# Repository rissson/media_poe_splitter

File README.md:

# Media PoE splitter

This board splits a PoE+ input into a 24V 85W output and a USB interface for data. It is meant to be used as part of my
home media system for driving in-wall speakers.

## Specs

- Uses a [Silvertel Ag5800](https://silvertel.com/ag5800/) for PoE control and DC-DC conversion
  - From PoE+ to PoE++ (Type 2 to Type 4, 802.3at and 802.3bt)
  - Outputs up to 85W of power over 24V
- Converts the data from 4 pairs Ethernet to USB 2.0 with a [Microchip 7850](https://www.microchip.com/en-us/product/lan7850)
  - 10/100/1000 Ethernet (but limited by USB 2.0 speed at around 400 Mbps)

## Usage

My usage of this board is with a
[HiFiBerry Amp2](https://www.hifiberry.com/shop/boards/dealing-with-blocked-p5-holes-7/) and a
[Raspberry Pi Zero 2 W](https://www.raspberrypi.com/products/raspberry-pi-zero-2-w/).

Power is provided to the Amp2, which in turns powers the RPi and drives 2 speakers.

Data is provided to the RPi via Micro USB 2.0. The data output of the `media_poe_splitter` is done over a flex ribbon
cable (pitch 0.5mm, 6pos) to fit dimension constraints. The associated `usb_breakout` board transforms that into a Micro
USB connector that can be plugged in the RPi data port.

## Considerations

Thermal management should be done accordingly to the recommendations provided by the Ag5800 documentation.

The board has 4 heat pads which should be coated using thermally conductive oxime board mounting the Ag5800.

## Datasheets and reference boards

- Ag5800
  - https://silvertel.com/images/datasheets/Ag5800-datasheet-%20IEEE802_3bt-Power-over-Ethernet-4-pair-PD.pdf
  - The EVALAg5800 schematic and BOMs are not publicly published by Silvertel, but they sent it over by email when asked
    for it. As such, I won't reproduce them here, but here are some public references for similar boards:
    - https://silvertel.com/images/Eval-Board-User-Guides/EVALAg5810-User-Manual.pdf
    - https://silvertel.com/images/Eval-Board-User-Guides/EvalAg59600-Board-User-Manual.pdf
- LAN7850
  - https://ww1.microchip.com/downloads/aemDocuments/documents/UNG/ProductDocuments/DataSheets/LAN7850-Data-Sheet-DS00001993F.pdf
  - https://www.farnell.com/datasheets/3109926.pdf
  - https://ww1.microchip.com/downloads/aemDocuments/documents/UNG/ProductDocuments/BoardDesignFiles/UNG8002_EVB_LAN7850_A1.pdf
- Wurth Elektronik PoE Ethernet to USB board
  - https://www.we-online.com/components/media/o758720v410%20RD022_EN.pdf

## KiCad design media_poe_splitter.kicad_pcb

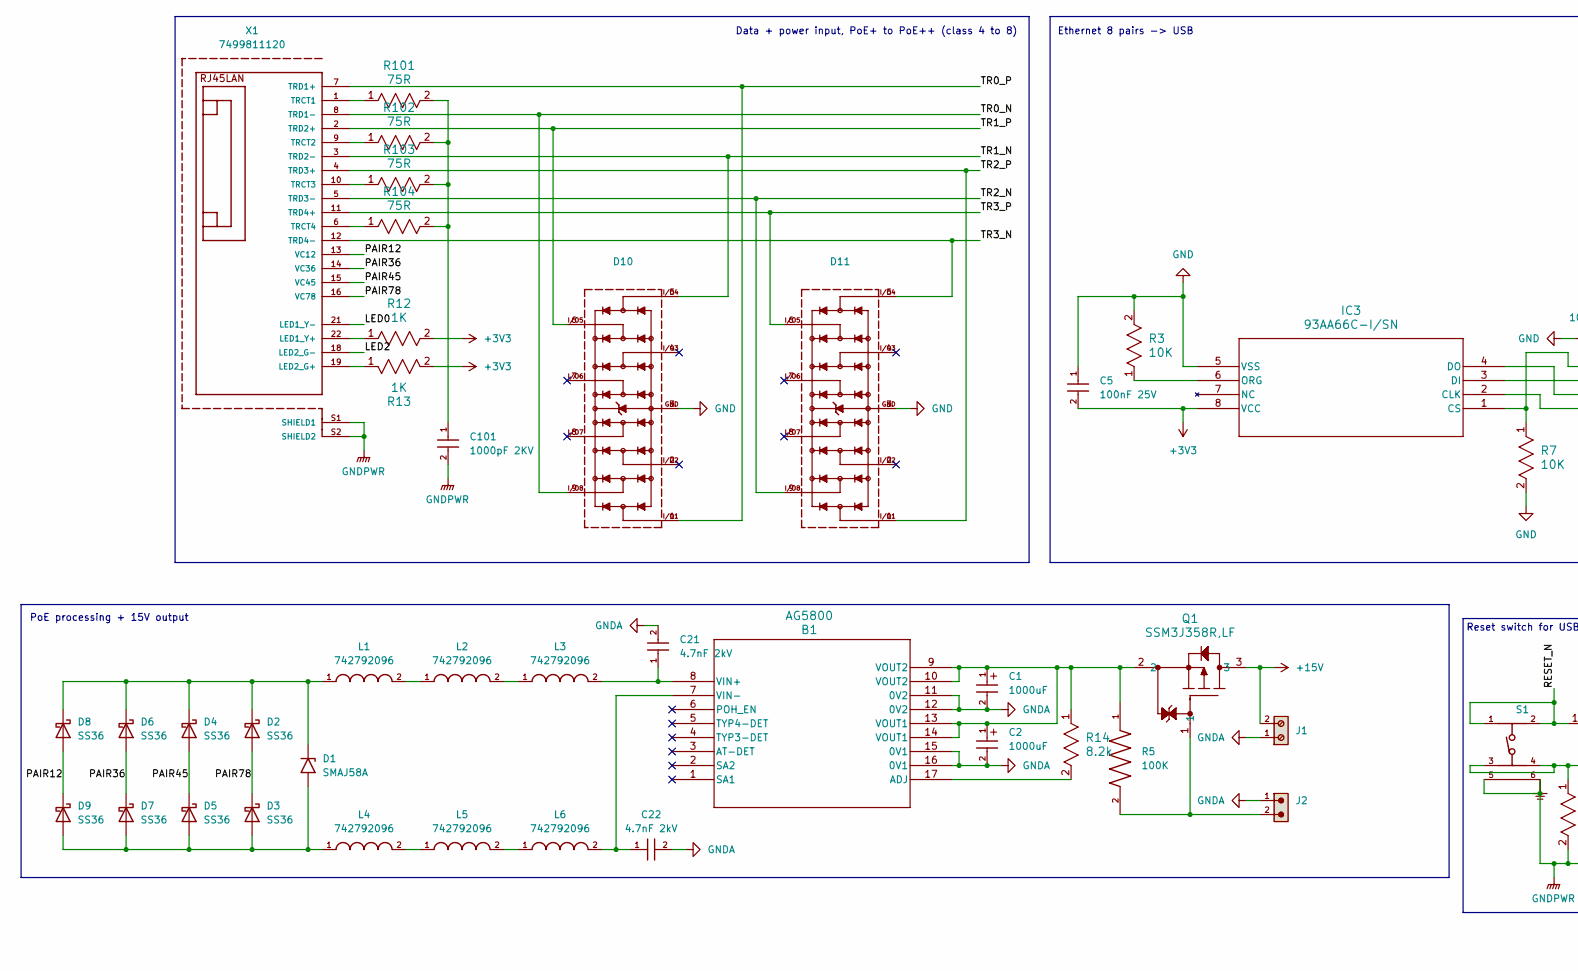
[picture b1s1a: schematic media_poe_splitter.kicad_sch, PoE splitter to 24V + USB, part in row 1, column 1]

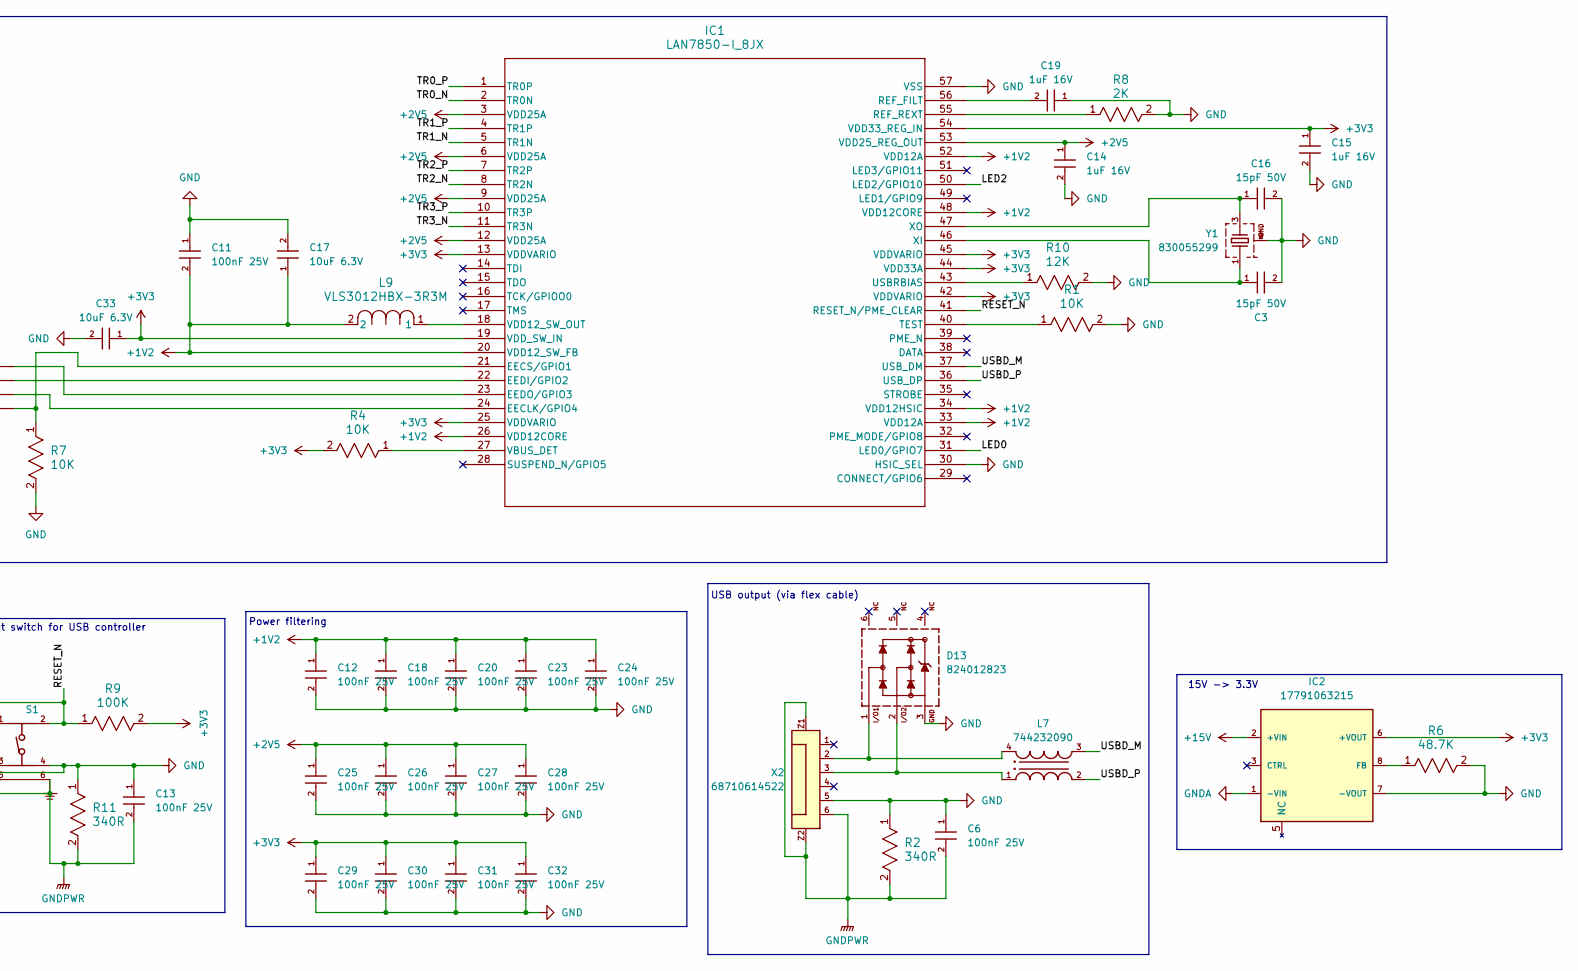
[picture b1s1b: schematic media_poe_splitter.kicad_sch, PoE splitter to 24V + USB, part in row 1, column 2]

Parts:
B1: AG5800; MPN Ag5800
C1, C2: 1000uF; 860020578018; MPN 860020578018
C3, C16: 15pF 50V; 885012005056; MPN 885012005056
C5, C6, C11, C12, C13, C18, C20, C23, C24, C25, C26, C27, C28, C29, C30, C31, C32: 100nF 25V; 885012206071; MPN 885012206071
C14, C15, C19: 1uF 16V; 885012206052; MPN 885012206052
C17, C33: 10uF 6.3V; 885012207003; MPN 885012207003
C21, C22: 4.7nF 2kV; 885342208020; MPN 885342208020
C101: 1000pF 2KV; 885342208024; MPN 885342208024
D1: SMAJ58A; D_SMA; MPN SMAJ58A
D2, D3, D4, D5, D6, D7, D8, D9: SS36; D_SMA; MPN SS36
D10, D11: 5Vdc; 824014885; MPN 824014885
D13: 824012823; MPN 824012823
IC1: LAN7850-I_8JX; MPN LAN7850-I/8JX
IC2: 17791063215; MPN 17791063215
IC3: 93AA66C-I/SN; 93AA66C-I_SN; MPN 93AA66C-I/SN
J1: Screw_Terminal_01x02; 691210910002; MPN 691210910002
J2: 61300211121; PART-NUMBER 61300211121
L1, L2, L3, L4, L5, L6: 742792096; MPN 742792096
L7: 744232090; MPN 744232090
L9: VLS3012HBX-3R3M; MPN VLS3012HBX-3R3M
Q1: SSM3J358R,LF; MPN SSM3J358R,LF
R1, R3, R4, R7: 10K; RC0603FR-0710KL; MPN RC0603FR-0710KL
R2, R11: 340R; RC0603FR-07340RL; MPN RC0603FR-07340RL
R5: 100K; RC1206FR-07100KL; MPN RC1206FR-07100KL
R6: 48.7K; RC0603FR-0748K7L; MPN RC0603FR-0748K7L
R8: 2K; RC0603FR-072KL; MPN RC0603FR-072KL
R9: 100K; RC0603FR-07100KL; MPN RC0603FR-07100KL
R10: 12K; RC0603FR-0712KL; MPN RC0603FR-0712KL
R12, R13: 1K; RC1206FR-071KL; MPN RC1206FR-071KL
R14: 8.2k; RC0603FR-078K2L; MPN RC0603FR-078K2L
R101, R102, R103, R104: 75R; RC0805FR-0775RL; MPN RC0805FR-0775RL
S1: 435151014824; MPN 435151014824
X1: 7499811120; MPN 7499811120
X2: 68710614522; MPN 68710614522
Y1: 830055299; MPN 830055299

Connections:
+1V2: C11.2, C12.1, C17.1, C18.1, C20.1, C23.1, C24.1, IC1.20 (VDD12_SW_FB), IC1.26 (VDD12CORE), IC1.33 (VDD12A), IC1.34 (VDD12HSIC), IC1.48 (VDD12CORE), IC1.52 (VDD12A), L9.2
+2V5: C14.1, C25.1, C26.1, C27.1, C28.1, IC1.3 (VDD25A), IC1.6 (VDD25A), IC1.9 (VDD25A), IC1.12 (VDD25A), IC1.53 (VDD25_REG_OUT)
+3V3: C5.2, C15.1, C29.1, C30.1, C31.1, C32.1, C33.1, IC1.13 (VDDVARIO), IC1.19 (VDD_SW_IN), IC1.25 (VDDVARIO), IC1.42 (VDDVARIO), IC1.44 (VDD33A), IC1.45 (VDDVARIO), IC1.54 (VDD33_REG_IN), IC2.6 (+VOUT), IC3.8 (VCC), R4.2, R9.2, R12.2, R13.2
+15V: IC2.2 (+VIN), J1.2, Q1.3
/LED0: IC1.31 (LED0/GPIO7), X1.21 (LED1_Y-)
/LED2: IC1.50 (LED2/GPIO10), X1.18 (LED2_G-)
/PAIR12: D8.2 (A), D9.1 (K), X1.13 (VC12)
/PAIR36: D6.2 (A), D7.1 (K), X1.14 (VC36)
/PAIR45: D4.2 (A), D5.1 (K), X1.15 (VC45)
/PAIR78: D2.2 (A), D3.1 (K), X1.16 (VC78)
/RESET_N: IC1.41 (RESET_N/PME_CLEAR), R9.1, S1.1, S1.2
/TR0_N: D10.9, IC1.2 (TR0N), X1.8 (TRD1-)
/TR0_P: D10.1, IC1.1 (TR0P), X1.7 (TRD1+)
/TR1_N: D10.5, IC1.5 (TR1N), X1.3 (TRD2-)
/TR1_P: D10.6, IC1.4 (TR1P), X1.2 (TRD2+)
/TR2_N: D11.9, IC1.8 (TR2N), X1.5 (TRD3-)
/TR2_P: D11.1, IC1.7 (TR2P), X1.4 (TRD3+)
/TR3_N: D11.5, IC1.11 (TR3N), X1.12 (TRD4-)
/TR3_P: D11.6, IC1.10 (TR3P), X1.11 (TRD4+)
/USBD_M: IC1.37 (USB_DM), L7.3
/USBD_P: IC1.36 (USB_DP), L7.2
GND: C3.2, C5.1, C6.1, C11.1, C12.2, C13.1, C14.2, C15.2, C16.2, C17.2, C18.2, C19.1, C20.2, C23.2, C24.2, C25.2, C26.2, C27.2, C28.2, C29.2, C30.2, C31.2, C32.2, C33.2, D10.3, D11.3, D13.3, IC1.30 (HSIC_SEL), IC1.57 (VSS), IC2.7 (-VOUT), IC3.5 (VSS), R1.2, R2.1, R3.2, R6.2, R7.2, R8.2, R10.2, R11.1, S1.3, S1.4, X2.5, Y1.2, Y1.4
GNDA: B1.11 (0V2), B1.12 (0V2), B1.15 (0V1), B1.16 (0V1), C1.2, C2.2, C21.2, C22.2, IC2.1 (-VIN), J1.1, J2.1
GNDPWR: C6.2, C13.2, C101.2, R2.2, R11.2, S1.5, S1.6, X1.S1 (SHIELD1), X1.S2 (SHIELD2), X2.6, X2.Z1, X2.Z2
unnamed: B1.17 (ADJ), R14.2
unnamed: B1.8 (VIN+), C21.1, L3.2
unnamed: B1.7 (VIN-), C22.1, L6.2
unnamed: B1.9 (VOUT2), B1.10 (VOUT2), B1.13 (VOUT1), B1.14 (VOUT1), C1.1, C2.1, Q1.2, R5.1, R14.1
unnamed: C101.1, R101.2, R102.2, R103.2, R104.2
unnamed: D1.1 (A1), D2.1 (K), D4.1 (K), D6.1 (K), D8.1 (K), L1.1
unnamed: D1.2 (A2), D3.2 (A), D5.2 (A), D7.2 (A), D9.2 (A), L4.1
unnamed: D13.1, L7.4, X2.2
unnamed: D13.2, L7.1, X2.3
unnamed: IC1.24 (EECLK/GPIO4), IC3.2 (CLK)
unnamed: IC1.21 (EECS/GPIO1), IC3.1 (CS), R7.1
unnamed: IC1.22 (EEDI/GPIO2), IC3.3 (DI)
unnamed: IC1.23 (EEDO/GPIO3), IC3.4 (DO)
unnamed: C19.2, IC1.56 (REF_FILT)
unnamed: IC1.55 (REF_REXT), R8.1
unnamed: IC1.40 (TEST), R1.1
unnamed: IC1.43 (USBRBIAS), R10.1
unnamed: IC1.27 (VBUS_DET), R4.1
unnamed: IC1.18 (VDD12_SW_OUT), L9.1
unnamed: C3.1, IC1.46 (XI), Y1.1
unnamed: C16.1, IC1.47 (XO), Y1.3
unnamed: IC2.8 (FB), R6.1
unnamed: IC3.6 (ORG), R3.1
unnamed: J2.2, Q1.1, R5.2
unnamed: L1.2, L2.1
unnamed: L2.2, L3.1
unnamed: L4.2, L5.1
unnamed: L5.2, L6.1
unnamed: R12.1, X1.22 (LED1_Y+)
unnamed: R13.1, X1.19 (LED2_G+)
unnamed: R101.1, X1.1 (TRCT1)
unnamed: R102.1, X1.9 (TRCT2)
unnamed: R103.1, X1.10 (TRCT3)
unnamed: R104.1, X1.6 (TRCT4)

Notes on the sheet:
Reset switch for USB controller
Data + power input, PoE+ to PoE++ (class 4 to 8)
USB output (via flex cable)
15V -> 3.3V
Power filtering
Ethernet 8 pairs -> USB
PoE processing + 15V output

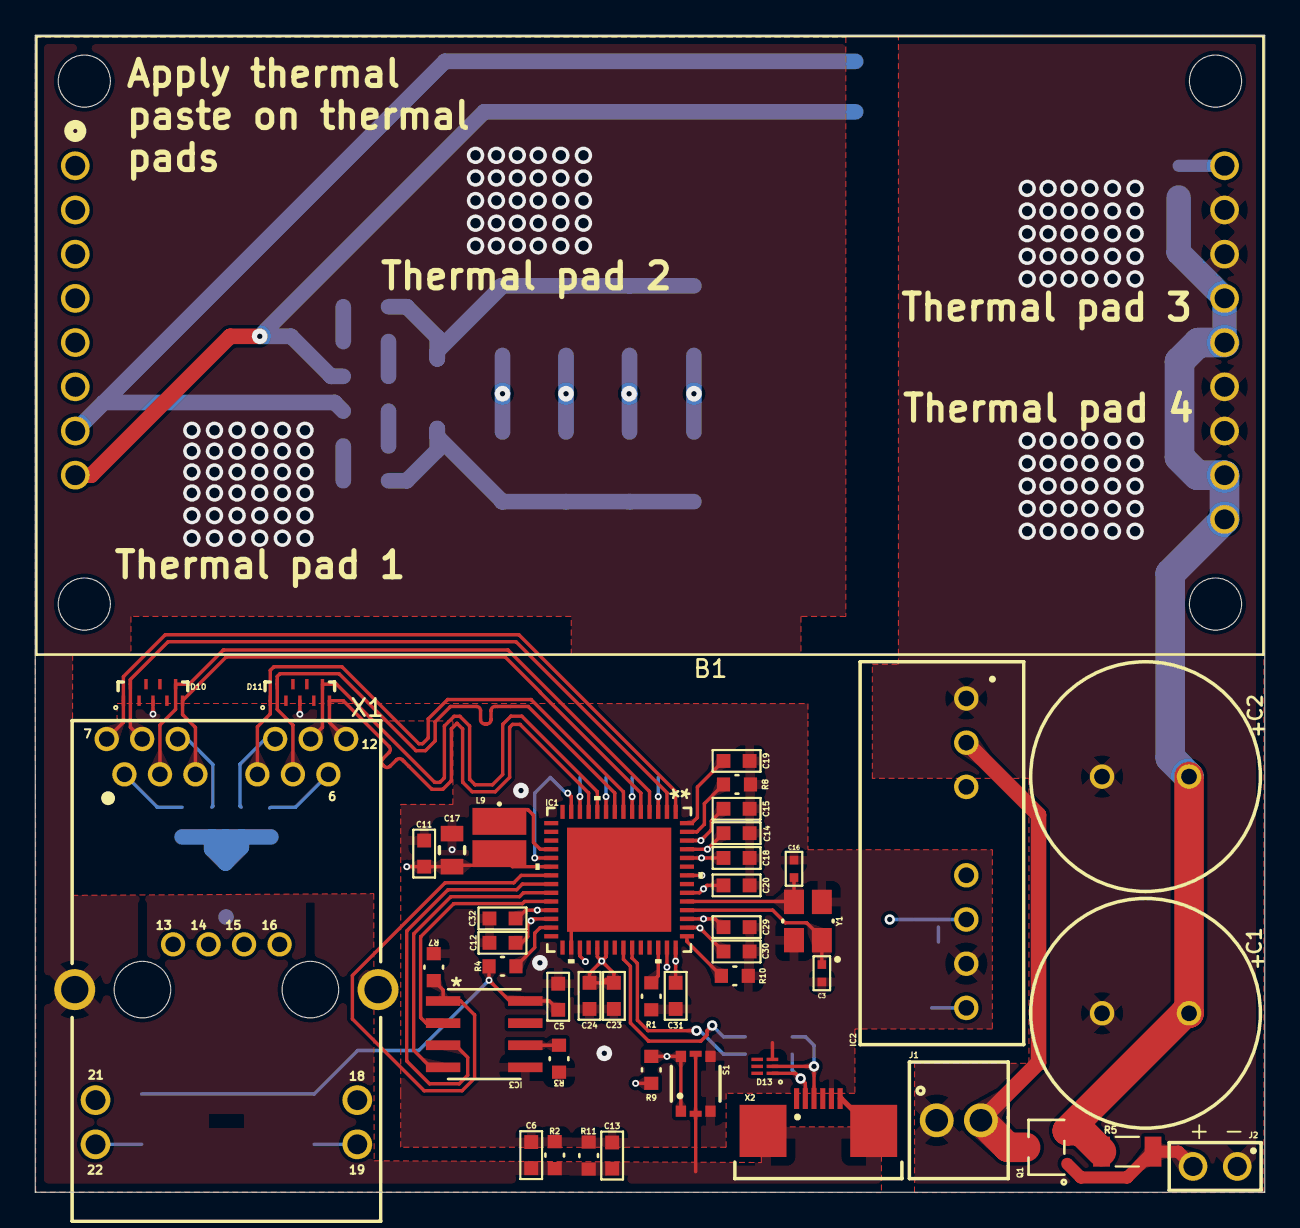
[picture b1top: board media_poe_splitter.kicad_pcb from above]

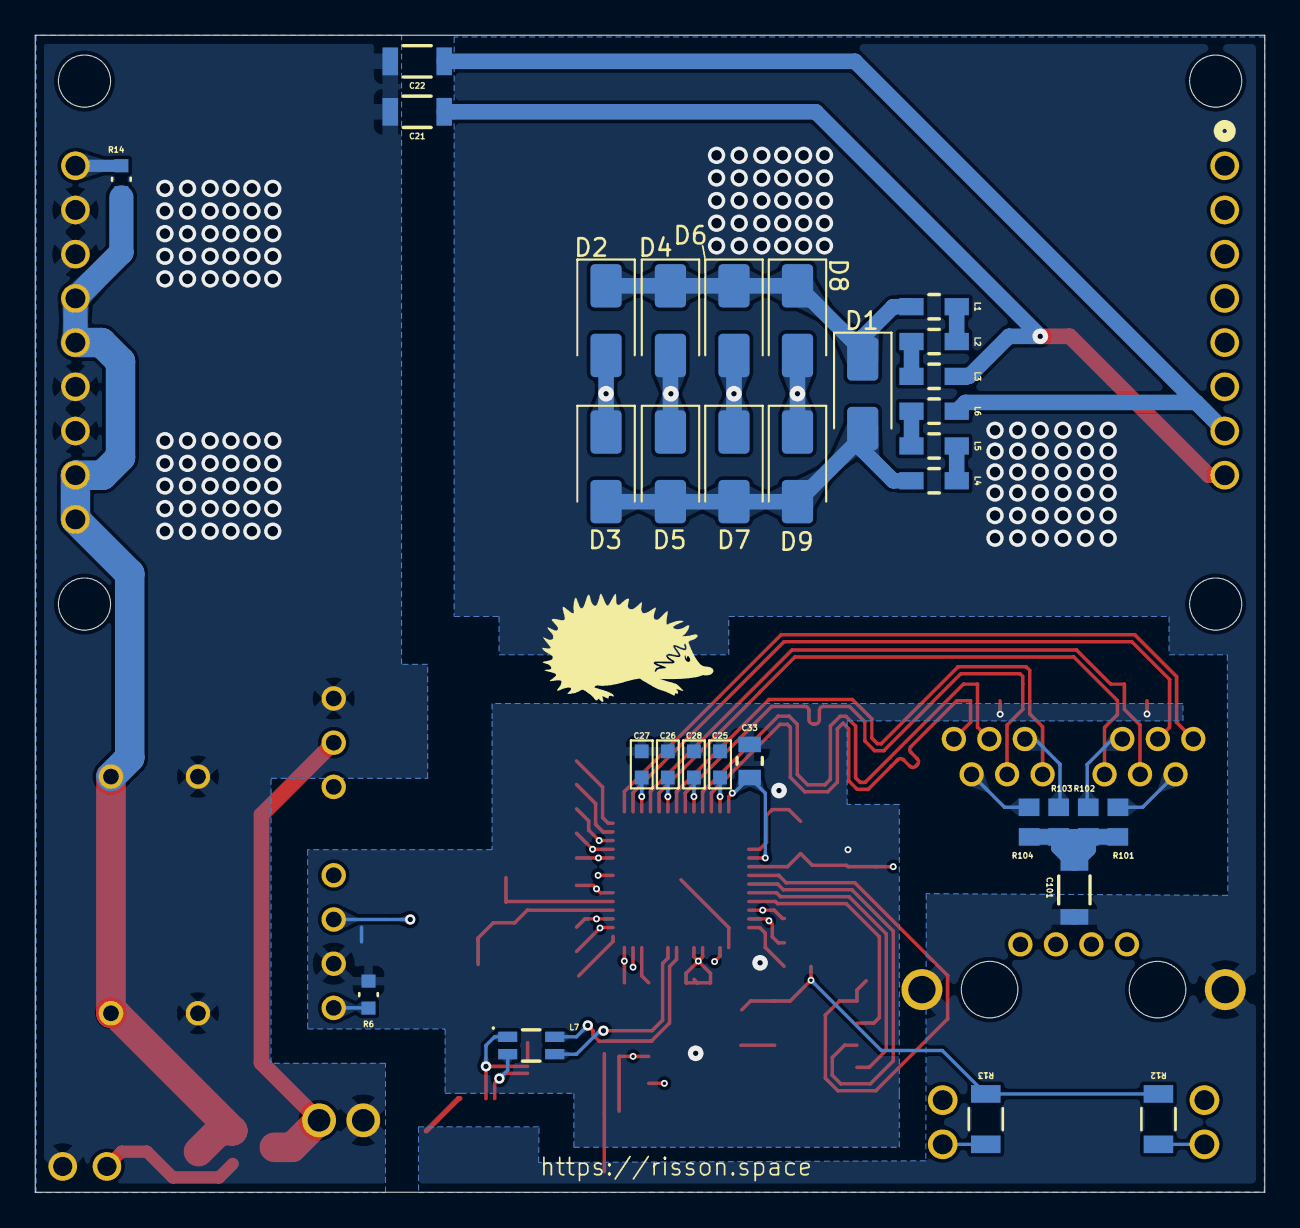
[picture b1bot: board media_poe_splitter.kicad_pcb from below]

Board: 4 copper layers, 70.7 x 66.5 mm, 78 parts (32 on the bottom side), 58 nets.

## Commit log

2025-01-22 Initial commit: PoE schematic and start of layout
2025-01-22 poe: add missing tracks
2025-01-25 add USB controller, finish board
2025-01-26 replace NLA part
2025-01-26 schematic: cleanup
2025-01-26 root: add license
2025-01-26 root: add readme
2025-01-26 board: try to make sure that ethernet tracks have the same length
2025-01-26 usb breakout: avoid vias in pad
2025-01-26 poe splitter: transform output to be in series to allow switching it off
2025-01-28 tweak traces a bit
2025-01-29 Add MOSFET to 24V output for enable/disable capability
2025-01-29 board: tweak track sizes and fill zones
2025-01-29 board: more zone tweaks, give clearance to ethernet pairs
2025-01-30 Add LEDs for Ethernet monitoring
2025-01-30 Remove useless via
2025-01-30 board, schematic: try to comply with ERC and DRC
2025-02-09 Update vias, add logos
2025-04-03 Fix voltage issues, bigger traces where needed
2025-04-03 gitignore: add database
